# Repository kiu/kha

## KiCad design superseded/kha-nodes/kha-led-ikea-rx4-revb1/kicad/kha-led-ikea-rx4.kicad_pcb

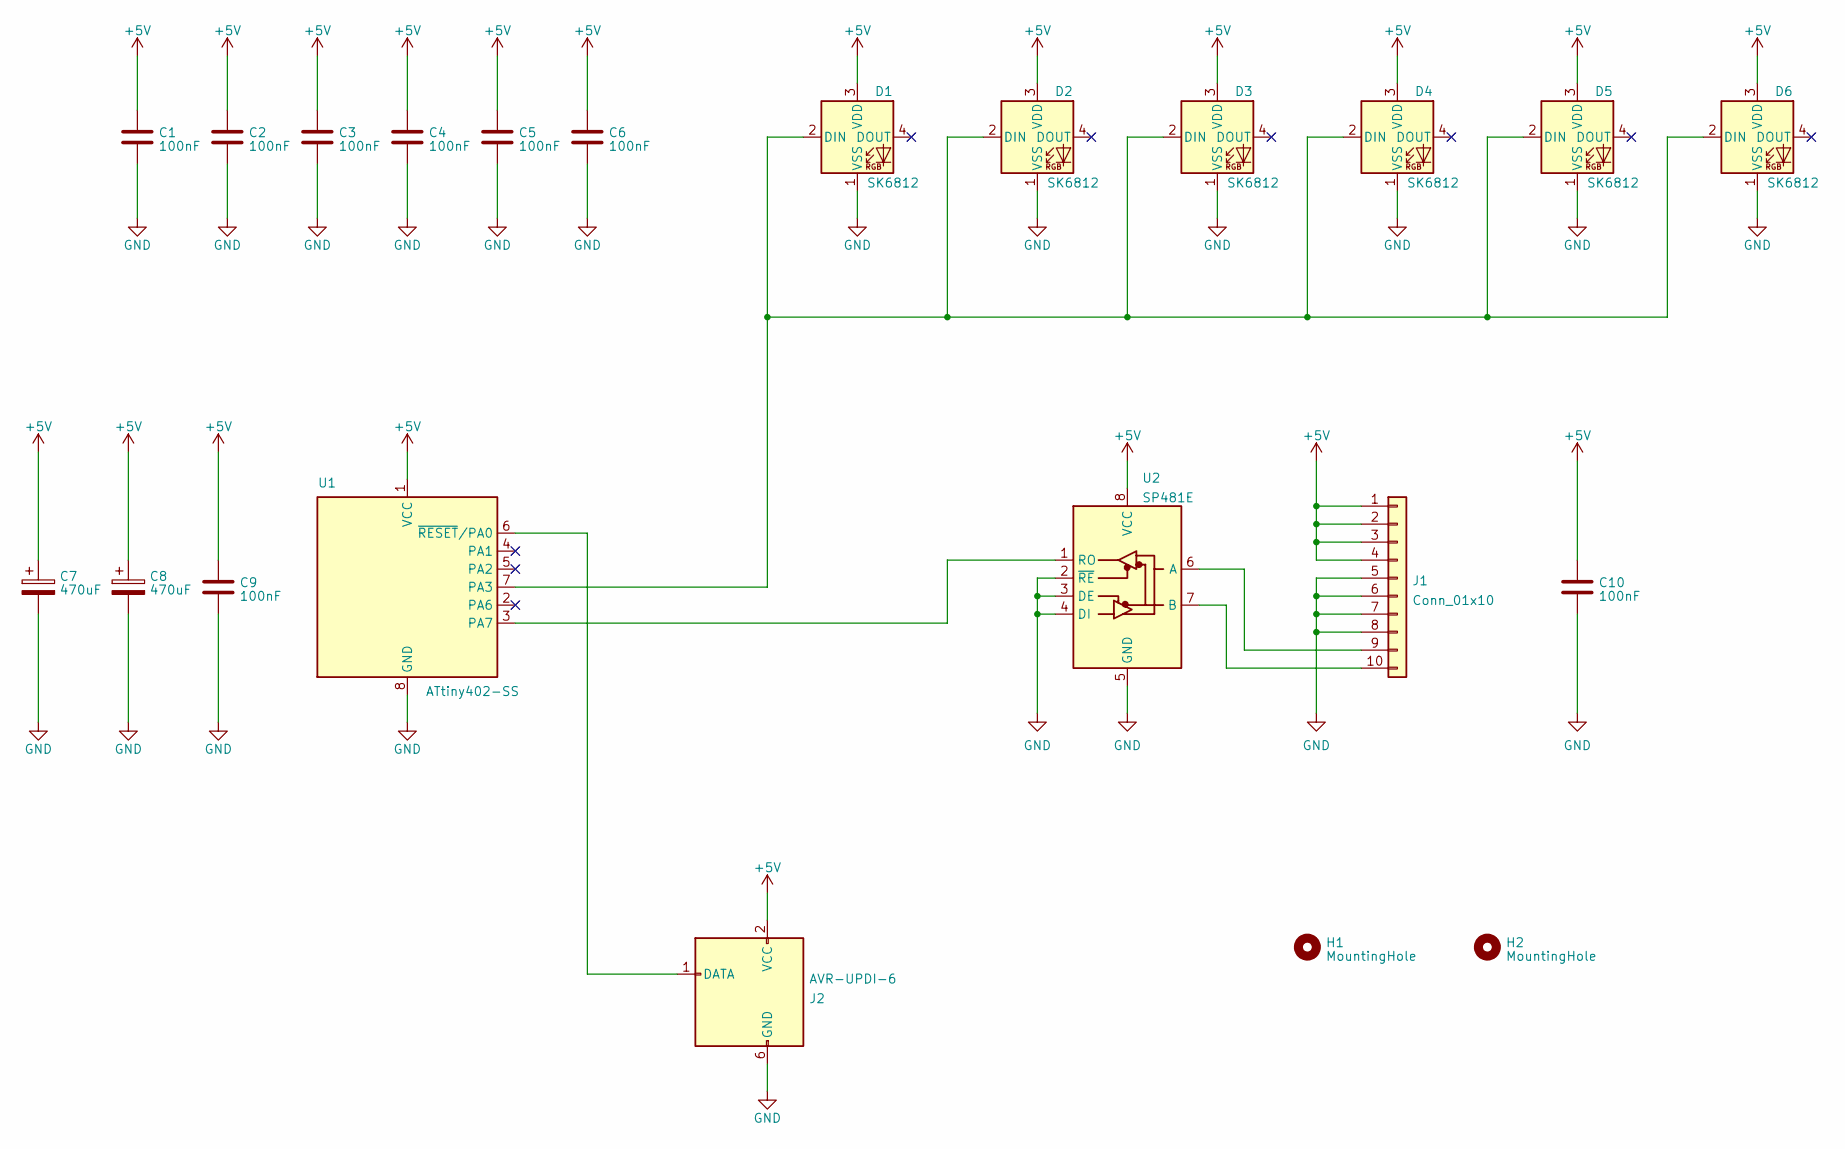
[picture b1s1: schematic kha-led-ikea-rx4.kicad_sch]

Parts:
C1, C2, C3, C4, C5, C6, C9, C10: 100nF; C_0805_2012Metric
C7, C8: 470uF; CP_EIA-6032-28_Kemet-C
D1, D2, D3, D4, D5, D6: SK6812; LED_SK6812_PLCC4_5.0x5.0mm_P3.2mm
H1, H2: MountingHole; MountingHole_3.2mm_M3_DIN965
J1: Conn_01x10; IDC-Header_2x05_P2.54mm_Vertical
J2: AVR-UPDI-6; eAVR6-UPDI-F
U1: ATtiny402-SS; SOIC-8_3.9x4.9mm_P1.27mm
U2: SP481E; SOIC-8_3.9x4.9mm_P1.27mm

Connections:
+5V: C1.1, C2.1, C3.1, C4.1, C5.1, C6.1, C7.1, C8.1, C9.1, C10.1, D1.3 (VDD), D2.3 (VDD), D3.3 (VDD), D4.3 (VDD), D5.3 (VDD), D6.3 (VDD), J1.1, J1.2, J1.3, J1.4, J2.2 (VCC), U1.1 (VCC), U2.8 (VCC)
GND: C1.2, C2.2, C3.2, C4.2, C5.2, C6.2, C7.2, C8.2, C9.2, C10.2, D1.1 (VSS), D2.1 (VSS), D3.1 (VSS), D4.1 (VSS), D5.1 (VSS), D6.1 (VSS), J1.5, J1.6, J1.7, J1.8, J2.6 (GND), U1.8 (GND), U2.2 (~RE), U2.3 (DE), U2.4 (DI), U2.5 (GND)
unnamed: D1.2 (DIN), D2.2 (DIN), D3.2 (DIN), D4.2 (DIN), D5.2 (DIN), D6.2 (DIN), U1.7 (PA3)
unnamed: J1.9, U2.6 (A)
unnamed: J1.10, U2.7 (B)
unnamed: J2.1 (DATA), U1.6 (~RESET/PA0)
unnamed: U1.3 (PA7), U2.1 (RO)

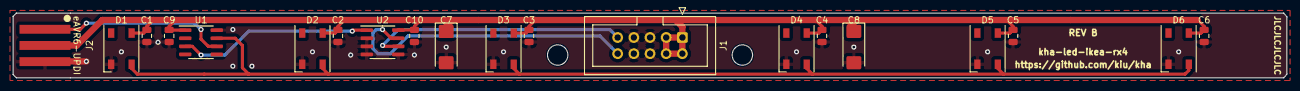
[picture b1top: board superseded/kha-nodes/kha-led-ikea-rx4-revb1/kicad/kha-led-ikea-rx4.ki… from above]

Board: 2 copper layers, 200.0 x 10.2 mm, 22 parts (0 on the bottom side), 7 nets.

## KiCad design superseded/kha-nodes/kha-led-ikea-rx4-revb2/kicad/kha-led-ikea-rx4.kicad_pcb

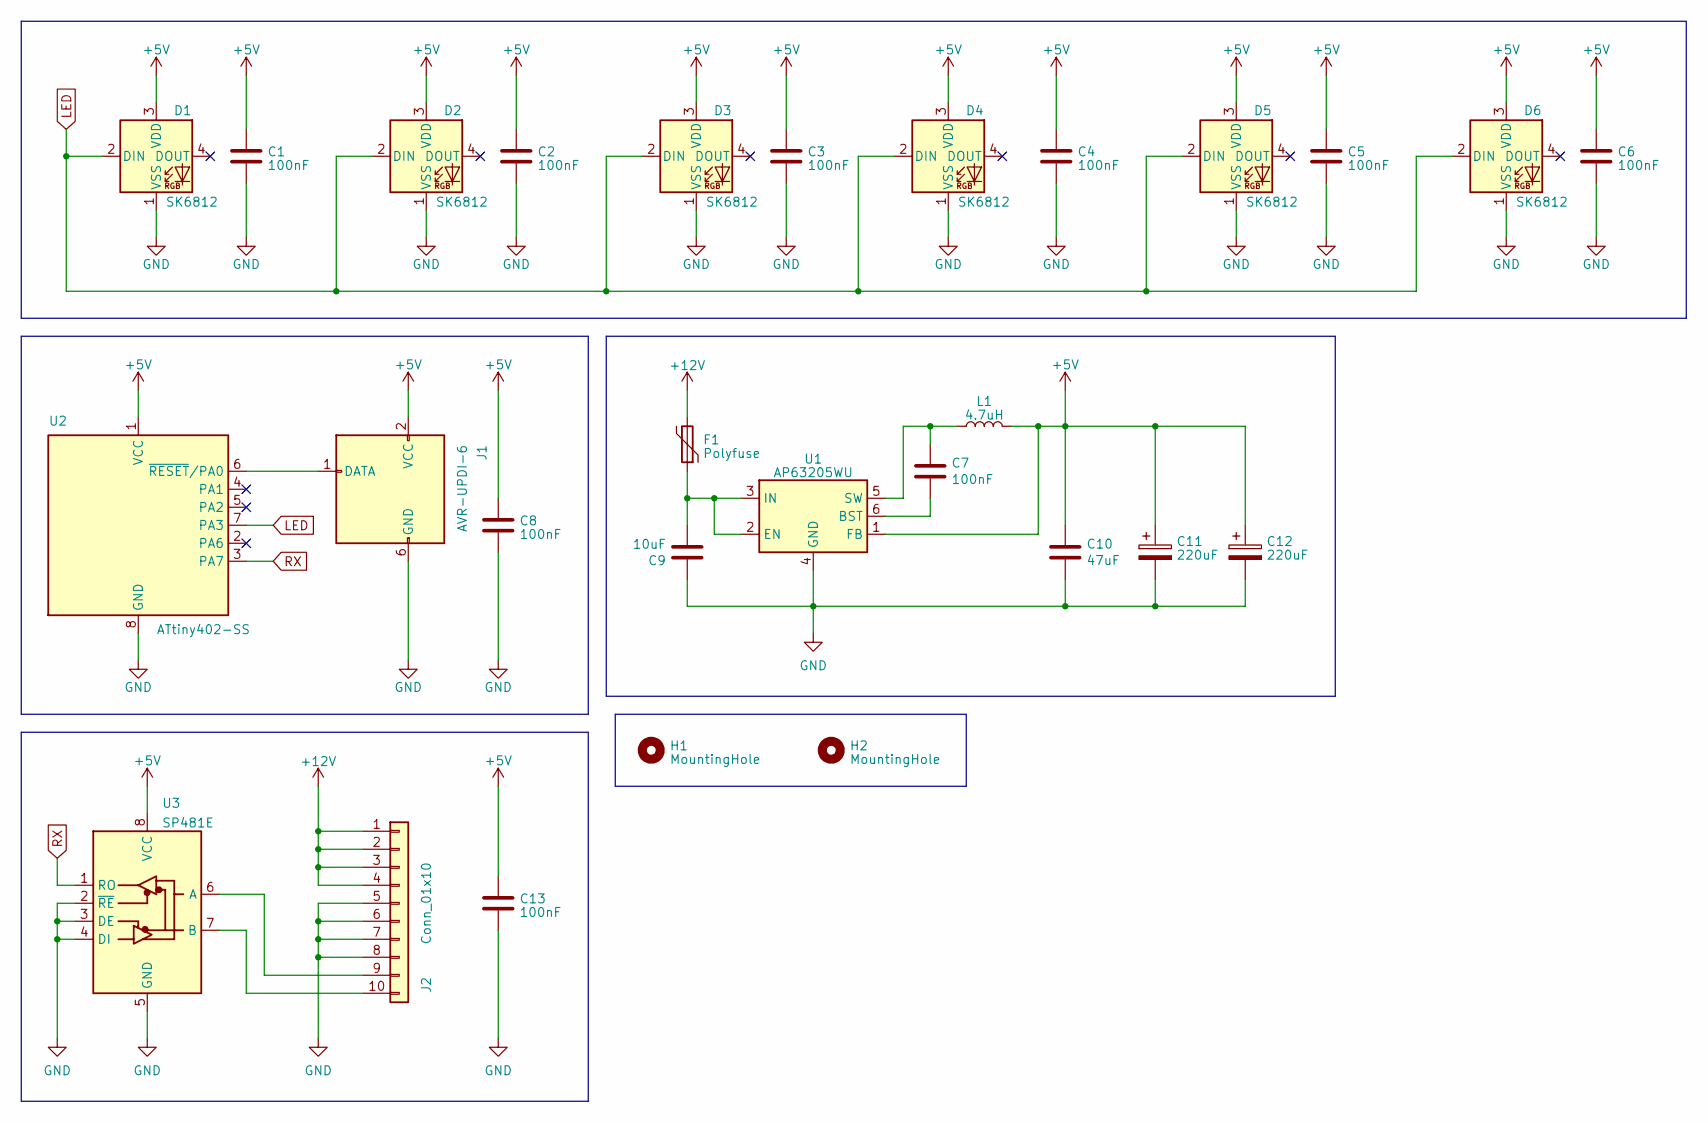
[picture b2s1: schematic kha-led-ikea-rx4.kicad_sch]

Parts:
C1, C2, C3, C4, C5, C6, C7, C8, C13: 100nF; C_0805_2012Metric
C9: 10uF; C_0805_2012Metric
C10: 47uF; C_1210_3225Metric
C11, C12: 220uF; CP_EIA-6032-28_Kemet-C
D1, D2, D3, D4, D5, D6: SK6812; LED_SK6812_PLCC4_5.0x5.0mm_P3.2mm
F1: Polyfuse; Fuse_0805_2012Metric
H1, H2: MountingHole; MountingHole_3.2mm_M3_DIN965
J1: AVR-UPDI-6; eAVR6-UPDI-F
J2: Conn_01x10; IDC-Header_2x05_P2.54mm_Vertical
L1: 4.7uH; L_1210_3225Metric
U1: AP63205WU; TSOT-23-6
U2: ATtiny402-SS; SOIC-8_3.9x4.9mm_P1.27mm
U3: SP481E; SOIC-8_3.9x4.9mm_P1.27mm

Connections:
+5V: C1.1, C2.1, C3.1, C4.1, C5.1, C6.1, C8.1, C10.1, C11.1, C12.1, C13.1, D1.3 (VDD), D2.3 (VDD), D3.3 (VDD), D4.3 (VDD), D5.3 (VDD), D6.3 (VDD), J1.2 (VCC), L1.2, U1.1 (FB), U2.1 (VCC), U3.8 (VCC)
+12V: F1.2, J2.1, J2.2, J2.3, J2.4
GND: C1.2, C2.2, C3.2, C4.2, C5.2, C6.2, C8.2, C9.1, C10.2, C11.2, C12.2, C13.2, D1.1 (VSS), D2.1 (VSS), D3.1 (VSS), D4.1 (VSS), D5.1 (VSS), D6.1 (VSS), J1.6 (GND), J2.5, J2.6, J2.7, J2.8, U1.4 (GND), U2.8 (GND), U3.2 (~RE), U3.3 (DE), U3.4 (DI), U3.5 (GND)
LED: D1.2 (DIN), D2.2 (DIN), D3.2 (DIN), D4.2 (DIN), D5.2 (DIN), D6.2 (DIN), U2.7 (PA3)
unnamed: J1.1 (DATA), U2.6 (~RESET/PA0)
unnamed: J2.9, U3.6 (A)
unnamed: J2.10, U3.7 (B)
unnamed: C7.2, U1.6 (BST)
unnamed: C9.2, F1.1, U1.2 (EN), U1.3 (IN)
unnamed: C7.1, L1.1, U1.5 (SW)
RX: U2.3 (PA7), U3.1 (RO)

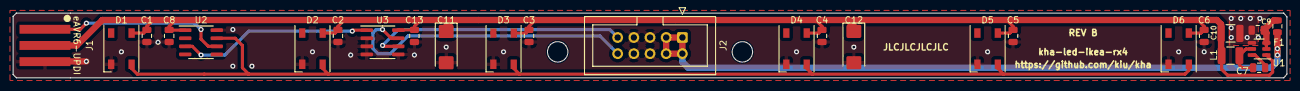
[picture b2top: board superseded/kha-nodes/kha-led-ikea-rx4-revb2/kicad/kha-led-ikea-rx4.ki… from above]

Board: 2 copper layers, 200.0 x 10.2 mm, 28 parts (0 on the bottom side), 11 nets.

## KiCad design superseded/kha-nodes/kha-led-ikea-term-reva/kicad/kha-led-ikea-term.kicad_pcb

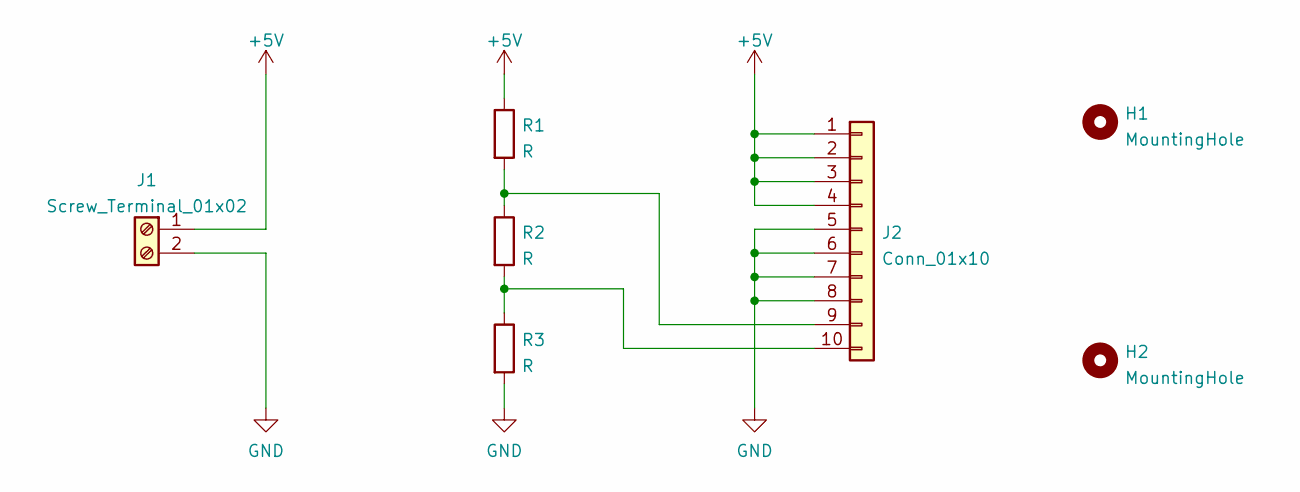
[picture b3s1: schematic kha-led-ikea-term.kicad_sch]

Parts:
H1, H2: MountingHole; MountingHole_3.2mm_M3
J1: Screw_Terminal_01x02; TerminalBlock_RND_205-00232_1x02_P5.08mm_Horizontal
J2: Conn_01x10; IDC-Header_2x05_P2.54mm_Vertical
R1, R2, R3: R; R_0805_2012Metric

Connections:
+5V: J1.1, J2.1, J2.2, J2.3, J2.4, R1.1
GND: J1.2, J2.5, J2.6, J2.7, J2.8, R3.2
unnamed: J2.9, R1.2, R2.1
unnamed: J2.10, R2.2, R3.1

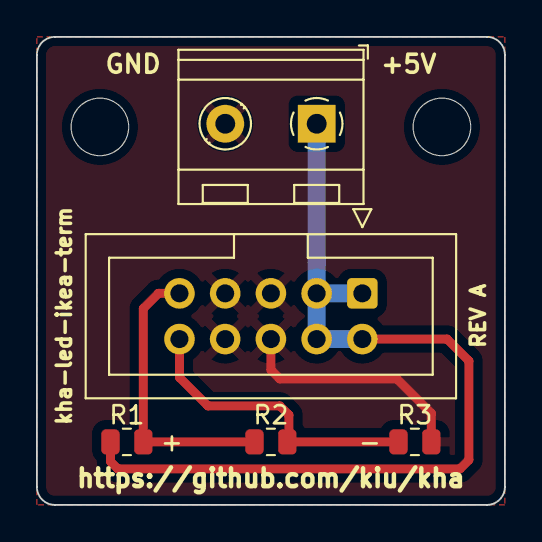
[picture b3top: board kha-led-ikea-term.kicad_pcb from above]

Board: 2 copper layers, 26.0 x 26.0 mm, 7 parts (0 on the bottom side), 4 nets.
